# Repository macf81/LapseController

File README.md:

# LapseController
Arduino based time lapse controller

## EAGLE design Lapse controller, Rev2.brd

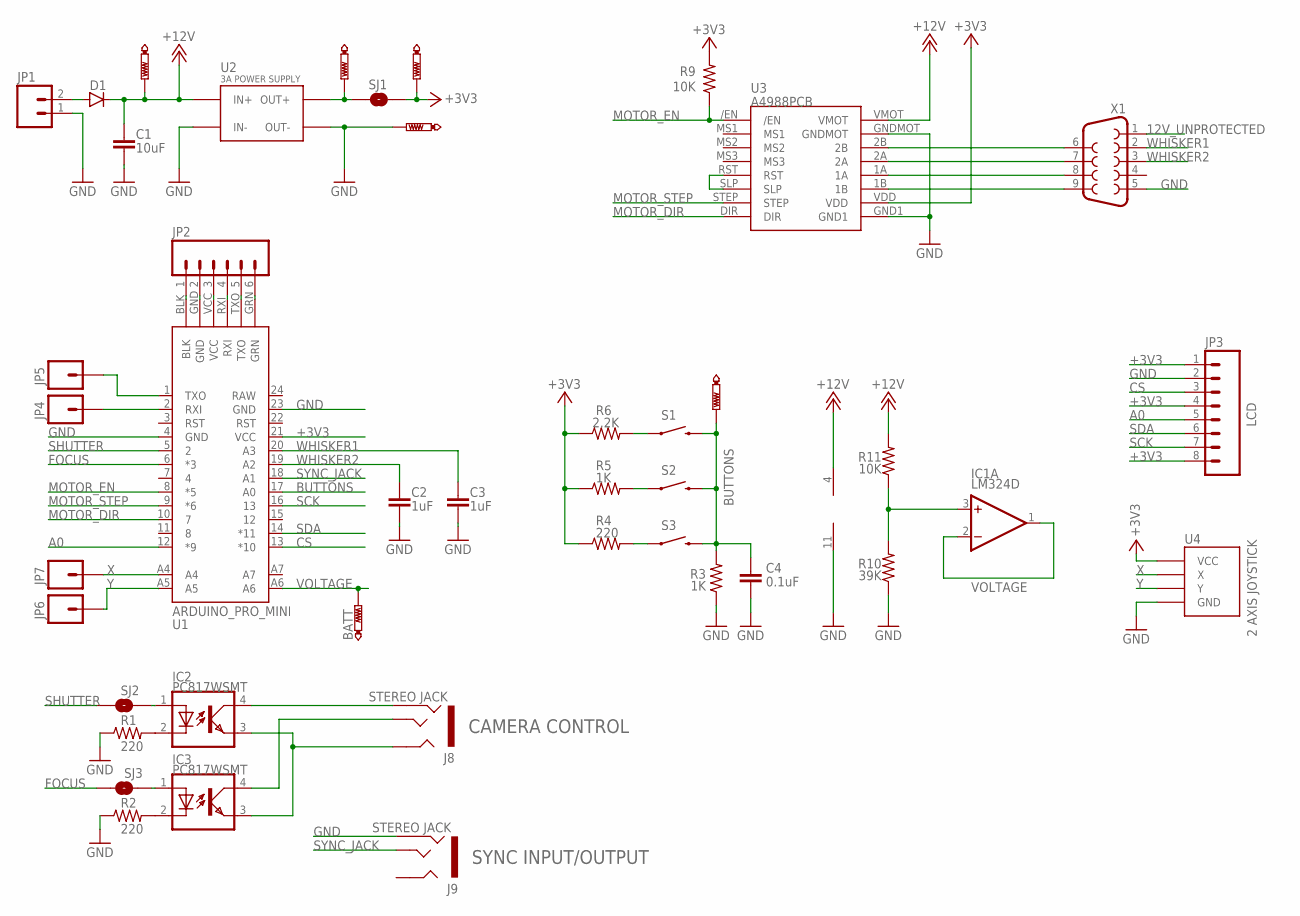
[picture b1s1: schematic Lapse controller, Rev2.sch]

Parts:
3.3V, 3.3V1, 12V: PTR1PAD1-13; P1-13
BATT: PTR1PAD1-13; P1-13
BUTTON: PTR1PAD1-13; P1-13
C1: 10uF; C0805K
C2, C3: 1uF; C0805K
C4: 0.1uF; C1206K
D1: DIODESMA; SMA-DIODE
GND: PTR1PAD1-13; P1-13
IC1: LM324D; SO14
IC2, IC3: PC817WSMT; WSMT
J8, J9: STEREO JACK; AUDIO-JACK-TRRS-SMD
JP1: M02PTH3; 1X02_LONGPADS
JP2: M06NO_SILK_FEMALE_PTH; 1X06_NO_SILK
JP3: LCD; 1X08_LONGPADS
JP4, JP5, JP6, JP7: M01OFFSET; 1X01_OFFSET
R1, R2, R4: 220; 1206
R3, R5: 1K; 1206
R6: 2.2K; 1206
R9, R11: 10K; 1206
R10: 39K; 1206
S1, S2, S3: SWITCH-MOMENTARY-212MM; TACTILE-PTH-12MM
SJ1: JUMPER-PAD-2-NOROUND; PAD-JUMPER-2-NO_YES_SILK_ROUND
SJ2, SJ3: JUMPER-PAD-2-NO; PAD-JUMPER-2-NO_NO_SILK
U1: ARDUINO_PRO_MINI
U2: 3A POWER SUPPLY; 3A_DC_DC_SUPERMINI_PWR_SUPPLY
U3: A4988PCB
U4: 2 AXIS JOYSTICK; 2WAY_JOYSTICK
X1: CONN; F09D

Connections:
12V_UNPROTECTED: D1.A, JP1.2, X1.1
+3V3: 3.3V.TP, JP3.1, JP3.4, JP3.8, R4.1, R5.1, R6.1, R9.2, SJ1.2, U1.21 (VCC), U3.VDD, U4.P$1 (VCC), U4.P$4 (VCC)
+12V: 12V.TP, C1.1, D1.C, IC1.4 (V+), R11.2, U2.IN+, U3.VMOT
A0: JP3.5, U1.12 (*9)
BUTTONS: BUTTON.TP, C4.1, R3.2, S1.3 (2), S2.3 (2), S3.3 (2), U1.17 (A0)
CS: JP3.3, U1.13 (*10)
FOCUS: SJ3.1, U1.6 (*3)
FOCUS_A: IC3.1 (A), SJ3.2
GND: C1.2, C2.2, C3.2, C4.2, GND.TP, IC1.11 (V-), J9.RING2A (RING2), J9.RING2B (RING2), JP1.1, JP3.2, R1.1, R2.1, R3.1, R10.1, U1.4 (GND), U1.23 (GND), U2.IN-, U2.OUT-, U3.GND1, U3.GNDMOT, U4.P$3 (GND), U4.P$6 (GND), X1.5
MOTOR_DIR: U1.10 (7), U3.DIR
MOTOR_EN: R9.1, U1.8 (*5), U3./EN
MOTOR_STEP: U1.9 (*6), U3.STEP
unnamed: 3.3V1.TP, SJ1.1, U2.OUT+
unnamed: IC2.2 (C), R1.2
unnamed: IC3.2 (C), R2.2
unnamed: IC2.4 (COL), J8.RING2A (RING2), J8.RING2B (RING2)
unnamed: IC2.3 (EMIT), IC3.3 (EMIT), J8.RING1A (RING1), J8.RING1B (RING1)
unnamed: IC3.4 (COL), J8.EARTH1 (TIP), J8.EARTH2 (TIP)
unnamed: R4.2, S3.1
unnamed: R5.2, S2.1
unnamed: R6.2, S1.1
unnamed: U3.RST, U3.SLP
unnamed: U3.2B, X1.6
unnamed: U3.2A, X1.7
unnamed: U3.1A, X1.8
unnamed: U3.1B, X1.9
unnamed: JP2.1, U1.BLK
unnamed: IC1.3 (+IN), R10.2, R11.1
unnamed: JP2.2, U1.GND
unnamed: JP2.3, U1.VCC
unnamed: JP2.4, U1.RXI
unnamed: JP2.5, U1.TXO
unnamed: JP2.6, U1.GRN
unnamed: JP4.1, U1.2 (RXI)
unnamed: JP5.1, U1.1 (TXO)
SCK: JP3.7, U1.16 (13)
SDA: JP3.6, U1.14 (*11)
SHUTTER: SJ2.1, U1.5 (2)
SHUTTER_A: IC2.1 (A), SJ2.2
SYNC_JACK: J9.EARTH1 (TIP), J9.EARTH2 (TIP), U1.18 (A1)
VOLTAGE: BATT.TP, IC1.1 (OUT), IC1.2 (-IN), U1.A6
WHISKER1: C3.1, U1.20 (A3), X1.2
WHISKER2: C2.1, U1.19 (A2), X1.3
X: JP7.1, U1.A4, U4.P$2 (X)
Y: JP6.1, U1.A5, U4.P$5 (Y)

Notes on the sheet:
CAMERA CONTROL
SYNC INPUT/OUTPUT

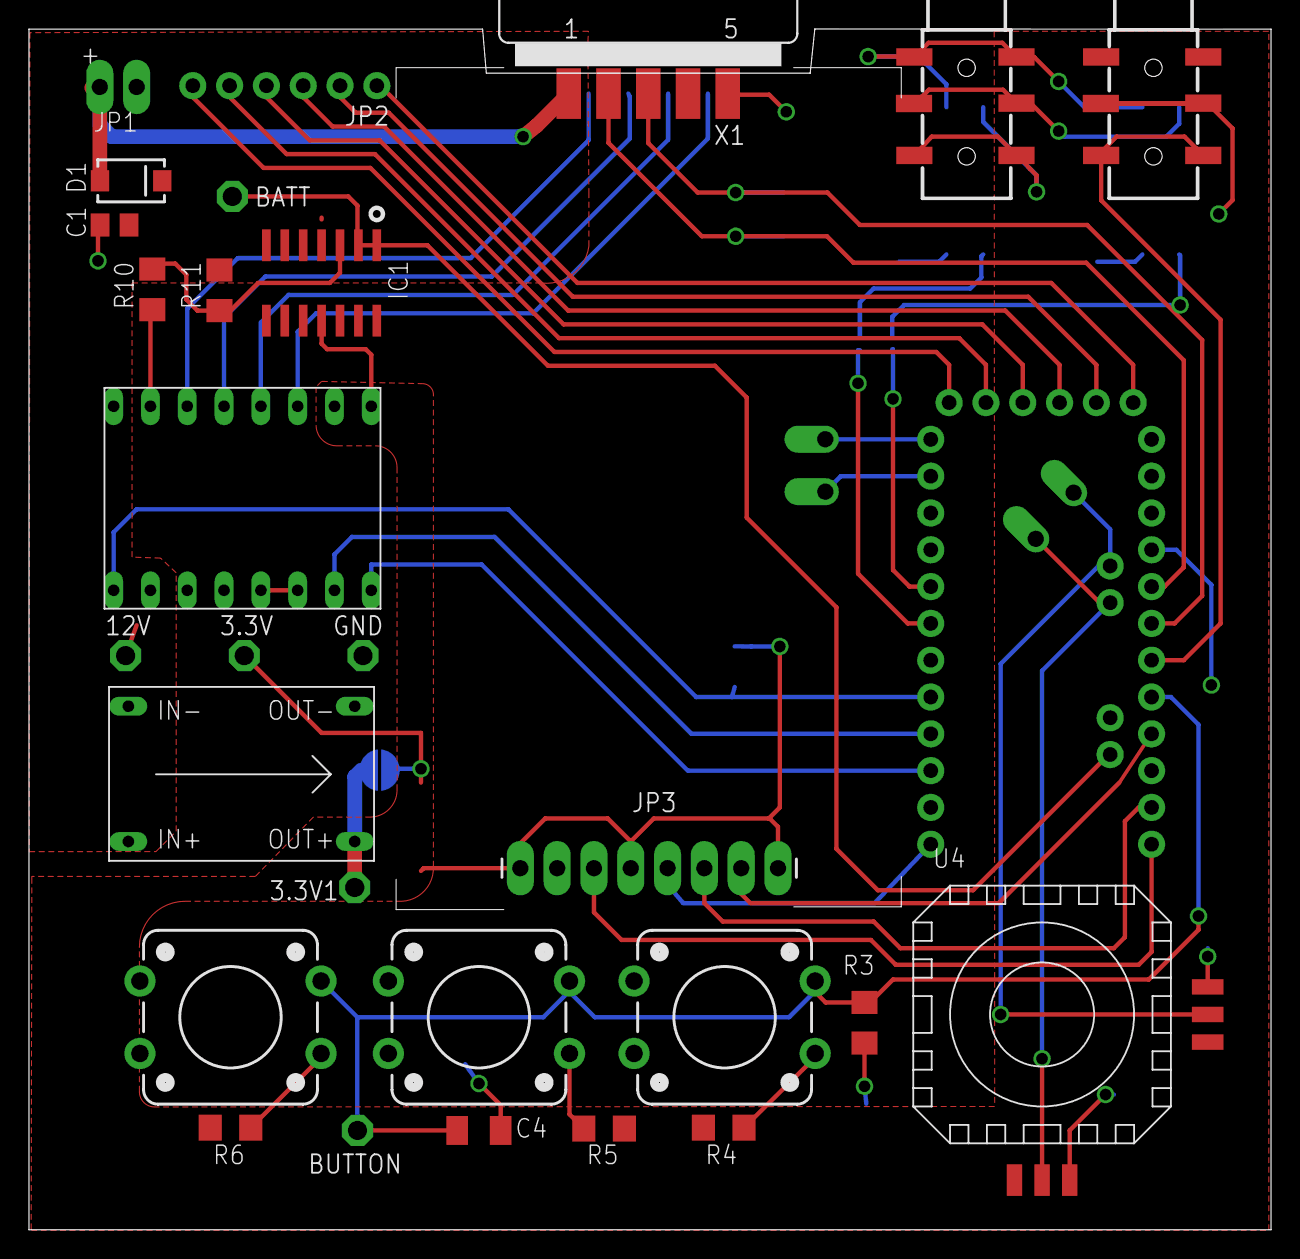
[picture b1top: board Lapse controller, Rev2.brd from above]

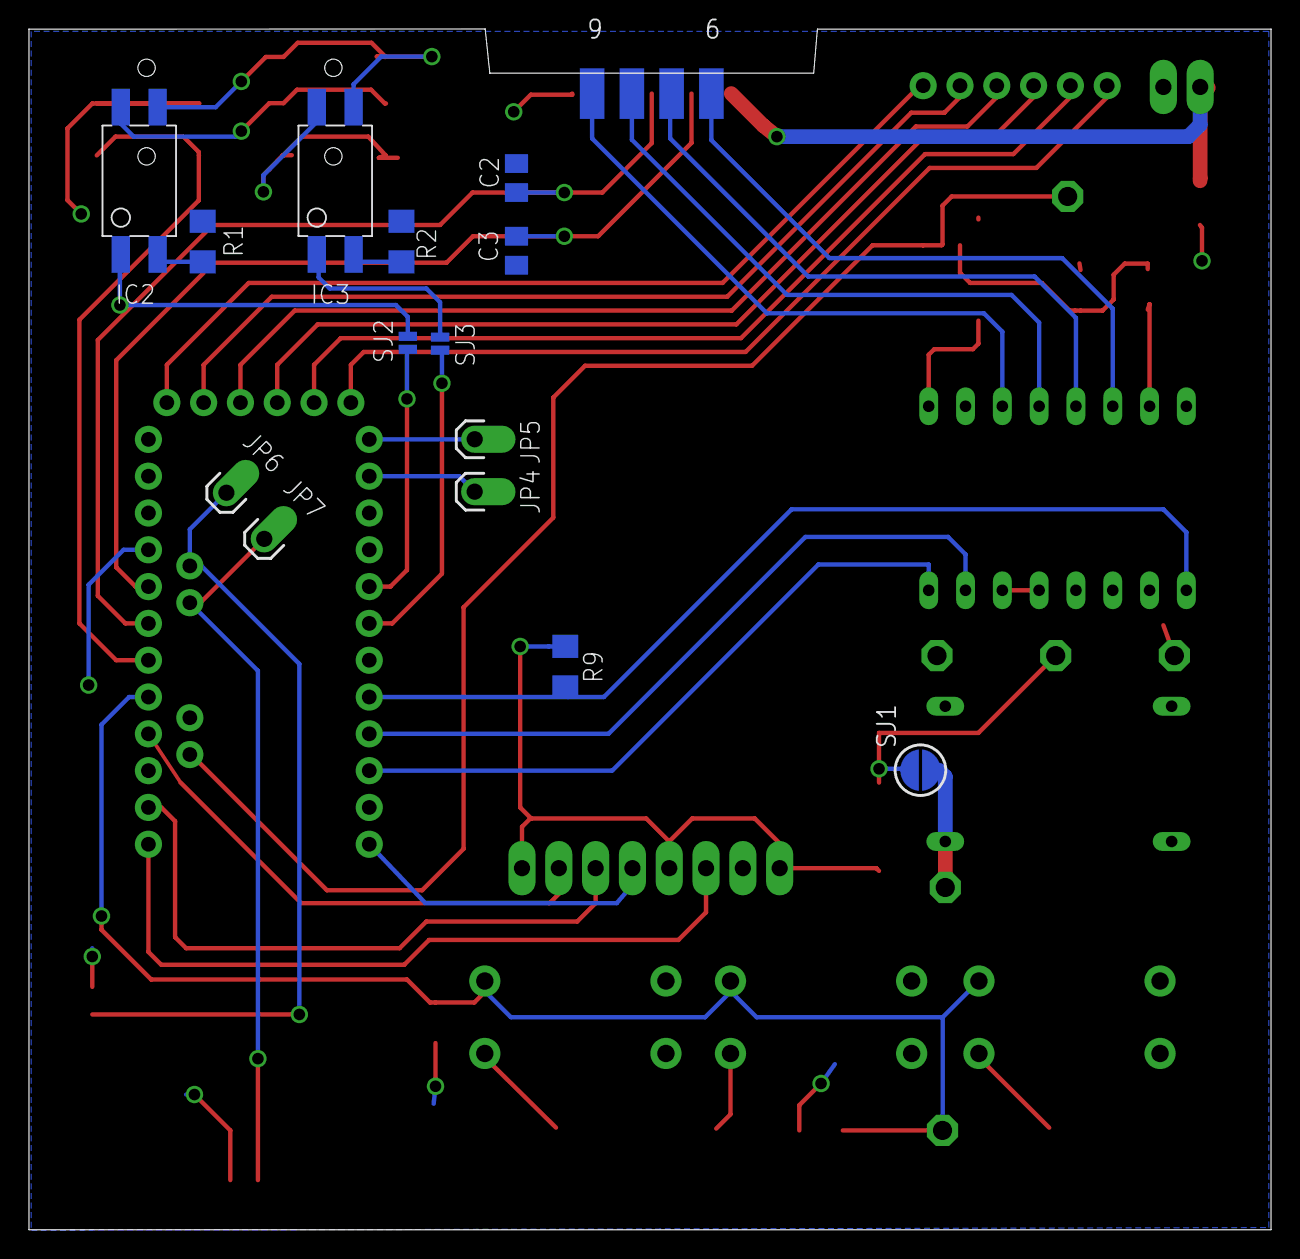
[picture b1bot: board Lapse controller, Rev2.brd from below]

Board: 2 copper layers, 85.7 x 82.9 mm, 43 parts (14 on the bottom side), 45 nets.

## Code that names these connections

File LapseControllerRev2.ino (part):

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//Pin definitions
Ucglib_ST7735_18x128x160_HWSPI ucg(/*cd=*/ 9 , /*cs=*/ 10, /*reset=*/ 8);

#define SHUTTER        2
#define SLEEP          5
#define STEP           6
#define DIR            7
#define FOCUS          8
#define BUTTON         A0
#define WHISKER2       A2
#define WHISKER1       A3
#define X_VALUE        A4
#define Y_VALUE        A5
#define VOLTAGE        A6

//Const definitions
const int k_joystick_down = -1;
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  pinMode(STEP, OUTPUT);
  pinMode(DIR, OUTPUT);
  pinMode(SLEEP, OUTPUT);
  pinMode(FOCUS, OUTPUT);
  pinMode(SHUTTER, OUTPUT);
  pinMode(WHISKER1, INPUT_PULLUP);
  pinMode(WHISKER2, INPUT_PULLUP);
  pinMode(VOLTAGE, INPUT);
  pinMode(X_VALUE, INPUT);
  pinMode(Y_VALUE, INPUT);

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
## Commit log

2016-04-15 Added files via upload
    First public release
2016-04-15 Added files via upload
2016-04-15 Added files via upload
    First public release for Lapse Controller firmware

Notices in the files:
parts and their libraries:
SparkFun-Connectors: Licensing: Creative Commons ShareAlike 4.0 International - https://creativecommons.org/licenses/by-sa/4.0
